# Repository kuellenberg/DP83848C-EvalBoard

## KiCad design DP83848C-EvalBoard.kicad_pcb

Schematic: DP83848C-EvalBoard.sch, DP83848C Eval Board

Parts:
H1, H2, H3, H4: MountingHole_Pad; MountingHole_3.2mm_M3_Pad_Via

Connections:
Earth: H1.1, H2.1, H3.1, H4.1; also elsewhere on the board

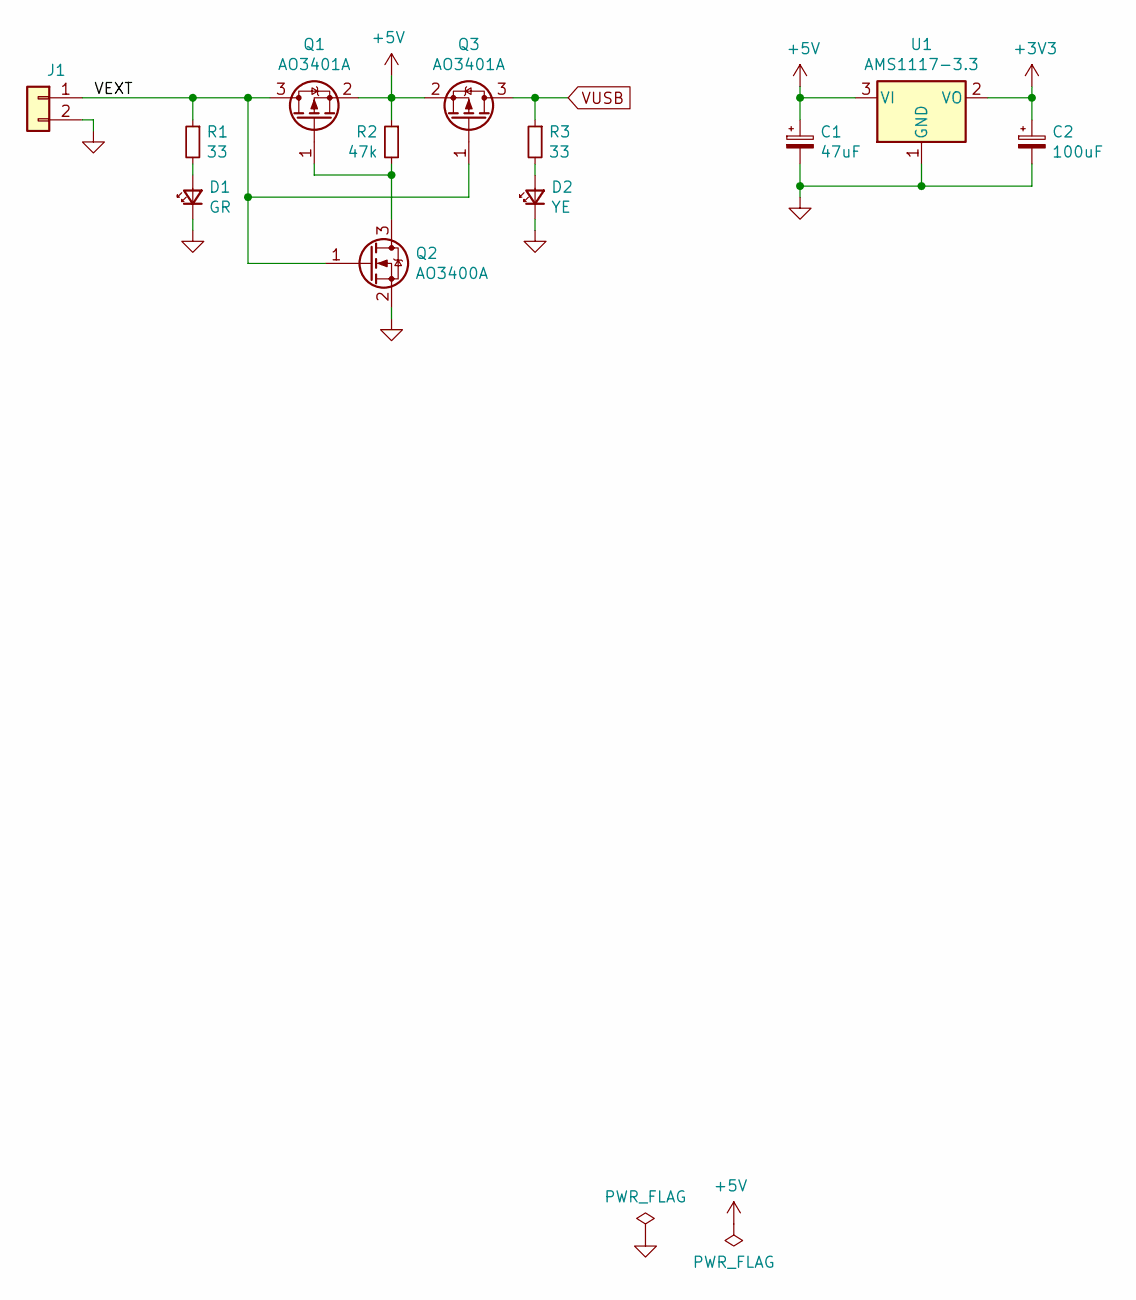
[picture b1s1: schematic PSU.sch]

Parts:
C1: 47uF; C_Elec_6.3x5.8; LCSC C178565
C2: 100uF; CP_EIA-3528-15_AVX-H; LCSC C16133
D1: GR; LED_0603_1608Metric; LCSC C72043
D2: YE; LED_0603_1608Metric; LCSC C72038
J1: Conn_01x02; Molex_022112022; Mouser 538-22-11-2022
Q1, Q3: AO3401A; SOT-23; LCSC C15127
Q2: AO3400A; SOT-23; LCSC C20917
R1, R3: 33; R_0402_1005Metric; LCSC C25105
R2: 47k; R_0402_1005Metric; LCSC C25792
U1: AMS1117-3.3; SOT-223-3_TabPin2; LCSC C6186

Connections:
+3V3: C2.1, U1.2 (VO); also elsewhere on the board
+5V: C1.1, Q1.2 (S), Q3.2 (S), R2.1, U1.3 (VI)
/PSU/VEXT: J1.1, Q1.3 (D), Q2.1 (G), Q3.1 (G), R1.1
GND: C1.2, C2.2, D1.1 (K), D2.1 (K), J1.2, Q2.2 (S), U1.1 (GND); also elsewhere on the board
unnamed: D1.2 (A), R1.2
unnamed: D2.2 (A), R3.2
unnamed: Q1.1 (G), Q2.3 (D), R2.2
VUSB: Q3.3 (D), R3.1; also elsewhere on the board

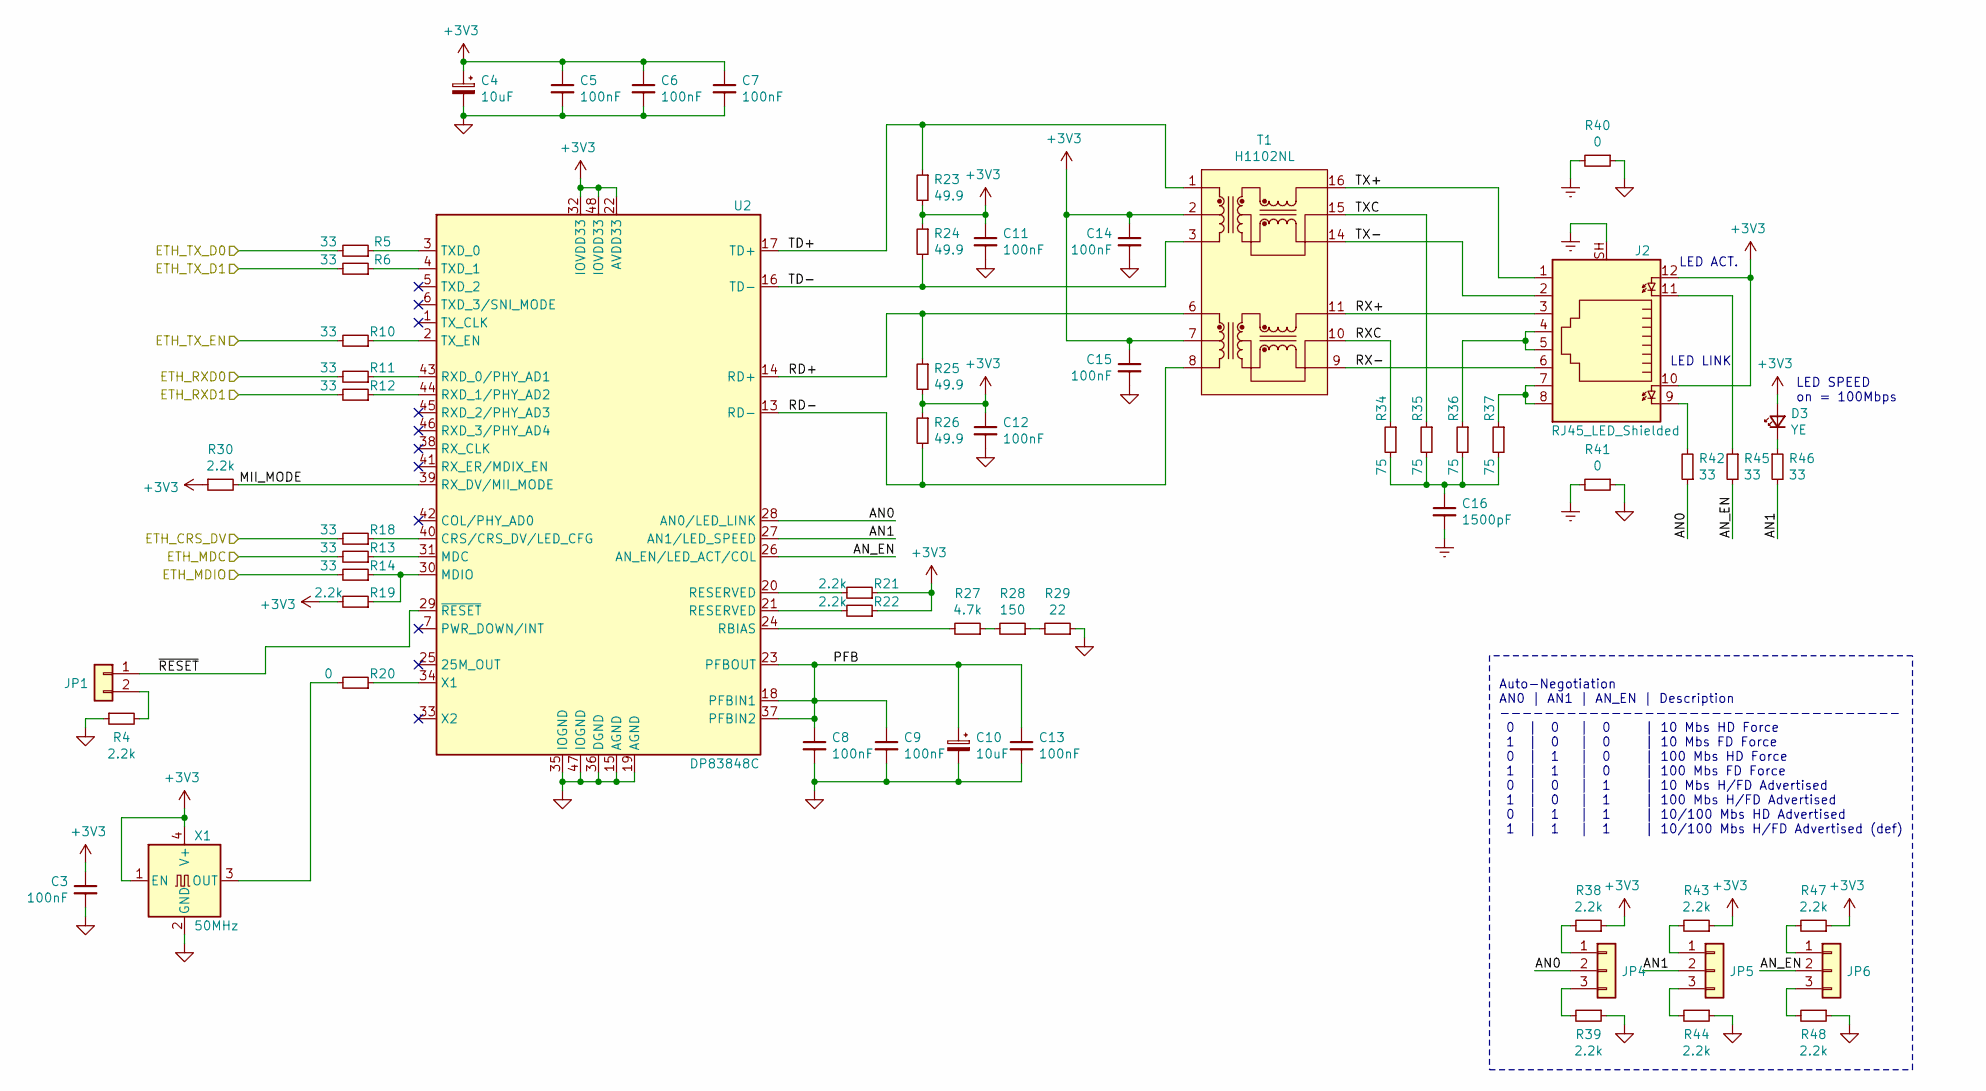
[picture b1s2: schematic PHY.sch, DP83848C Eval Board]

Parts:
C3, C5, C6, C7, C8, C9, C11, C12, C13, C14, C15: 100nF; C_0402_1005Metric; LCSC C1525
C4, C10: 10uF; CP_EIA-3216-18_Kemet-A; LCSC C7171
C16: 1500pF; C_0402_1005Metric; LCSC C23967
D3: YE; LED_0603_1608Metric; LCSC C72038
J2: RJ45_LED_Shielded; RJ45_Amphenol_RJHSE538X
JP1: Conn_01x02; PinHeader_1x02_P2.54mm_Vertical
JP4, JP5, JP6: Conn_01x03; PinHeader_1x03_P2.54mm_Vertical
R4, R19, R21, R22, R30, R38, R39, R43, R44, R47, R48: 2.2k; R_0402_1005Metric; LCSC C25879
R5, R6, R10, R11, R12, R13, R14, R18, R42, R45, R46: 33; R_0402_1005Metric; LCSC C25105
R20: 0; R_0402_1005Metric; LCSC C17168
R23, R24, R25, R26: 49.9; R_0402_1005Metric; LCSC C25120
R27: 4.7k; R_0402_1005Metric; LCSC C25900
R28: 150; R_0402_1005Metric; LCSC C25082
R29: 22; R_0402_1005Metric; LCSC C25092
R34, R35, R36, R37: 75; R_0402_1005Metric; LCSC C25133
R40, R41: 0; R_1206_3216Metric; LCSC C17888
T1: H1102NL; Transformer_Pulse_H1100NL; LCSC C18584
U2: DP83848C; LQFP-48_7x7mm_P0.5mm; LCSC C16688
X1: 50MHz; Oscillator_SMD_EuroQuartz_XO32-4Pin_3.2x2.5mm; LCSC C717684

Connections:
+3V3: C3.1, C4.1, C5.1, C6.1, C7.1, C11.1, C12.1, C14.1, C15.1, D3.2 (A), J2.10, J2.12, R19.2, R21.1, R22.1, R23.2, R24.1, R25.2, R26.1, R30.1, R38.1, R43.1, R47.1, T1.2, T1.7, U2.22 (AVDD33), U2.32 (IOVDD33), U2.48 (IOVDD33), X1.1 (EN), X1.4 (V+); also elsewhere on the board
/ETH_CRS_DV: R18.2; also elsewhere on the board
/ETH_MDC: R13.2; also elsewhere on the board
/ETH_MDIO: R14.2; also elsewhere on the board
/ETH_RXD0: R11.2; also elsewhere on the board
/ETH_RXD1: R12.2; also elsewhere on the board
/ETH_TX_D0: R5.2; also elsewhere on the board
/ETH_TX_D1: R6.2; also elsewhere on the board
/ETH_TX_EN: R10.2; also elsewhere on the board
/PHY/AN0: JP4.2, R42.1, U2.28 (AN0/LED_LINK)
/PHY/AN1: JP5.2, R46.2, U2.27 (AN1/LED_SPEED)
/PHY/AN_EN: JP6.2, R45.2, U2.26 (AN_EN/LED_ACT/COL)
/PHY/MII_MODE: R30.2, U2.39 (RX_DV/MII_MODE)
/PHY/PFB: C8.1, C9.1, C10.1, C13.1, U2.18 (PFBIN1), U2.23 (PFBOUT), U2.37 (PFBIN2)
/PHY/RD+: R25.1, T1.6, U2.14 (RD+)
/PHY/RD-: R26.2, T1.8, U2.13 (RD-)
/PHY/RX+: J2.3, T1.11
/PHY/RX-: J2.6, T1.9
/PHY/RXC: R34.1, T1.10
/PHY/TD+: R23.1, T1.1, U2.17 (TD+)
/PHY/TD-: R24.2, T1.3, U2.16 (TD-)
/PHY/TX+: J2.1, T1.16
/PHY/TX-: J2.2, T1.14
/PHY/TXC: R35.1, T1.15
/PHY/~RESET: JP1.1, U2.29 (~RESET~)
Earth: C16.2, J2.SH, R40.2, R41.2; also elsewhere on the board
GND: C3.2, C4.2, C5.2, C6.2, C7.2, C8.2, C9.2, C10.2, C11.2, C12.2, C13.2, C14.2, C15.2, R4.1, R29.1, R39.1, R40.1, R41.1, R44.1, R48.1, U2.15 (AGND), U2.19 (AGND), U2.35 (IOGND), U2.36 (DGND), U2.47 (IOGND), X1.2 (GND); also elsewhere on the board
unnamed: C16.1, R34.2, R35.2, R36.2, R37.2
unnamed: D3.1 (K), R46.1
unnamed: J2.4, J2.5, R36.1
unnamed: J2.7, J2.8, R37.1
unnamed: J2.9, R42.2
unnamed: J2.11, R45.1
unnamed: JP1.2, R4.2
unnamed: JP4.1, R38.2
unnamed: JP4.3, R39.2
unnamed: JP5.1, R43.2
unnamed: JP5.3, R44.2
unnamed: JP6.1, R47.2
unnamed: JP6.3, R48.2
unnamed: R5.1, U2.3 (TXD_0)
unnamed: R6.1, U2.4 (TXD_1)
unnamed: R10.1, U2.2 (TX_EN)
unnamed: R11.1, U2.43 (RXD_0/PHY_AD1)
unnamed: R12.1, U2.44 (RXD_1/PHY_AD2)
unnamed: R13.1, U2.31 (MDC)
unnamed: R14.1, R19.1, U2.30 (MDIO)
unnamed: R18.1, U2.40 (CRS/CRS_DV/LED_CFG)
unnamed: R20.1, U2.34 (X1)
unnamed: R20.2, X1.3 (OUT)
unnamed: R21.2, U2.20 (RESERVED)
unnamed: R22.2, U2.21 (RESERVED)
unnamed: R27.1, R28.2
unnamed: R27.2, U2.24 (RBIAS)
unnamed: R28.1, R29.2

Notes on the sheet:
Auto-Negotiation AN0 | AN1 | AN_EN | Description ------------------------------------ 0 | 0 | 0 | 10 Mbs HD Force 1 | 0 | 0 | 10 Mbs FD Force 0 | 1 | 0 | 100 Mbs HD Force 1 | 1 | 0 | 100 Mbs FD Force 0 | 0 | 1 | 10 Mbs H/FD Advertised 1 | 0 | 1 | 100 Mbs H/FD Advertised 0 | 1 | 1 | 10/100 Mbs HD Ad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
LED ACT.
LED LINK
LED SPEED on = 100Mbps

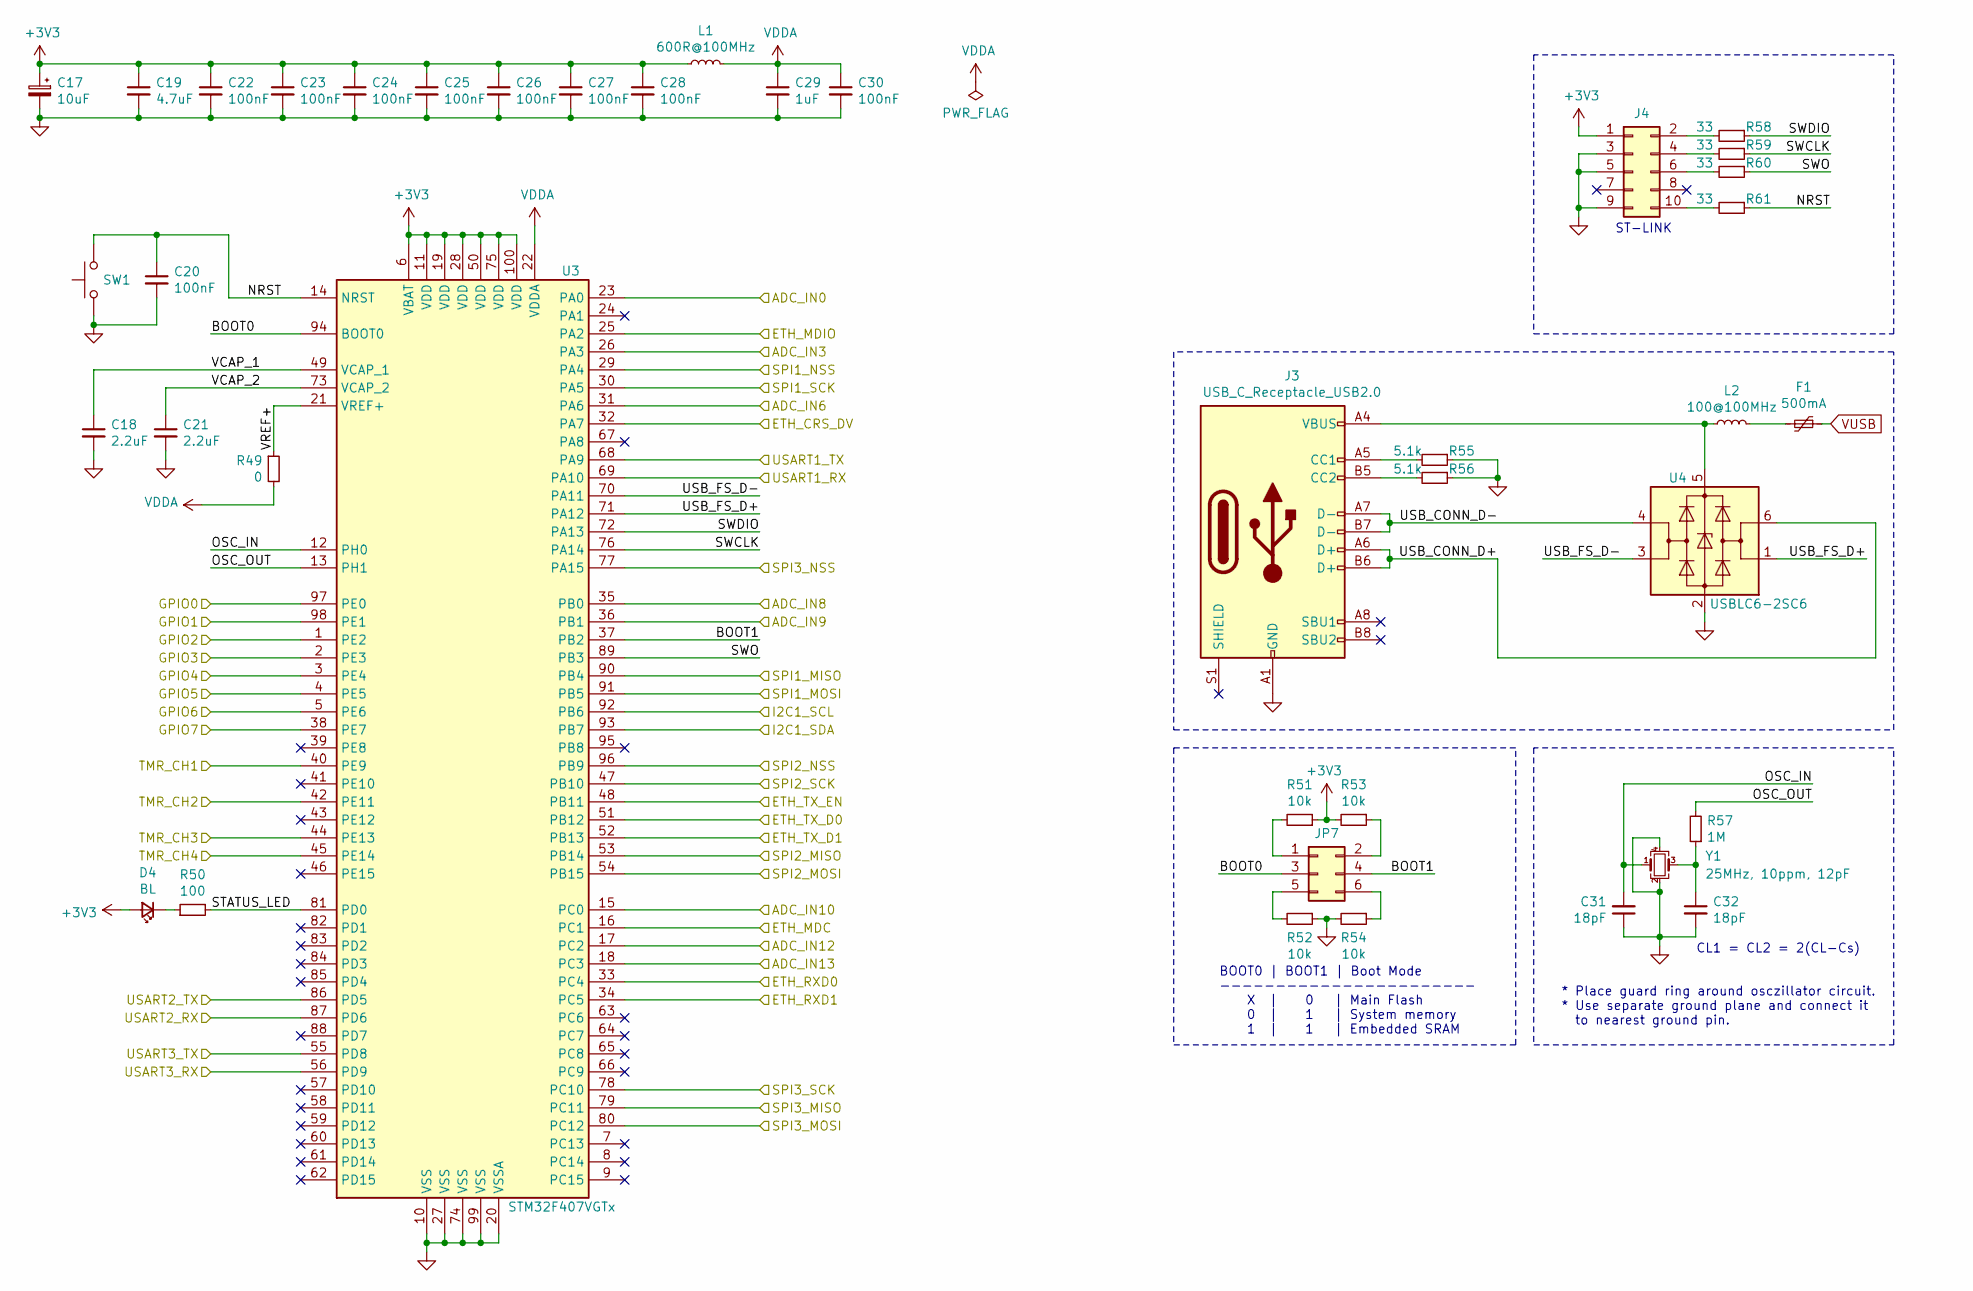
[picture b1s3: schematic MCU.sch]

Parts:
C17: 10uF; CP_EIA-3216-18_Kemet-A; LCSC C7171
C18, C21: 2.2uF; C_0603_1608Metric; LCSC C23630
C19: 4.7uF; C_0402_1005Metric; LCSC C23733
C20, C22, C23, C24, C25, C26, C27, C28, C30: 100nF; C_0402_1005Metric; LCSC C1525
C29: 1uF; C_0402_1005Metric; LCSC C52923
C31, C32: 18pF; C_0402_1005Metric; LCSC C1549
D4: BL; LED_0603_1608Metric; LCSC C72041
F1: 500mA; Fuse_1812_4532Metric_Castellated; Mouser 576-1812L050/60MR
J3: USB_C_Receptacle_USB2.0; DX07S016JA3R1500; Mouser 656-DX07S016JA3R1500
J4: Conn_02x05_Odd_Even; PinHeader_2x05_P2.54mm_Vertical
JP7: Conn_02x03_Odd_Even; PinHeader_2x03_P2.54mm_Vertical
L1: 600R@100MHz; L_0805_2012Metric; LCSC C1002
L2: 100@100MHz; L_0805_2012Metric; LCSC C1015
R49: 0; R_0402_1005Metric; LCSC C17168
R50: 100; R_0402_1005Metric; LCSC C25076
R51, R52, R53, R54: 10k; R_0402_1005Metric; LCSC C25744
R55, R56: 5.1k; R_0402_1005Metric; LCSC C25905
R57: 1M; R_0402_1005Metric; LCSC C26083
R58, R59, R60, R61: 33; R_0402_1005Metric; LCSC C25105
SW1: SW_Push; SW_PUSH_6mm; Mouser 611-PTS645SK432
U3: STM32F407VGTx; LQFP-100_14x14mm_P0.5mm; LCSC C28730
U4: USBLC6-2SC6; SOT-23-6; LCSC C558442
Y1: 25MHz, 10ppm, 12pF; Crystal_SMD_3225-4Pin_3.2x2.5mm; LCSC C9006

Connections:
+3V3: C17.1, C19.1, C22.1, C23.1, C24.1, C25.1, C26.1, C27.1, C28.1, D4.2 (A), J4.1, L1.1, R51.1, R53.2, U3.6 (VBAT), U3.11 (VDD), U3.19 (VDD), U3.28 (VDD), U3.50 (VDD), U3.75 (VDD), U3.100 (VDD); also elsewhere on the board
/ETH_CRS_DV: U3.32 (PA7); also elsewhere on the board
/ETH_MDC: U3.16 (PC1); also elsewhere on the board
/ETH_MDIO: U3.25 (PA2); also elsewhere on the board
/ETH_RXD0: U3.33 (PC4); also elsewhere on the board
/ETH_RXD1: U3.34 (PC5); also elsewhere on the board
/ETH_TX_D0: U3.51 (PB12); also elsewhere on the board
/ETH_TX_D1: U3.52 (PB13); also elsewhere on the board
/ETH_TX_EN: U3.48 (PB11); also elsewhere on the board
/IO/ADC0: U3.23 (PA0); also elsewhere on the board
/IO/ADC1: U3.26 (PA3); also elsewhere on the board
/IO/ADC2: U3.31 (PA6); also elsewhere on the board
/IO/ADC3: U3.35 (PB0); also elsewhere on the board
/IO/ADC4: U3.36 (PB1); also elsewhere on the board
/IO/ADC5: U3.15 (PC0); also elsewhere on the board
/IO/ADC6: U3.17 (PC2); also elsewhere on the board
/IO/ADC7: U3.18 (PC3); also elsewhere on the board
/IO/GPIO0: U3.97 (PE0); also elsewhere on the board
/IO/GPIO1: U3.98 (PE1); also elsewhere on the board
/IO/GPIO2: U3.1 (PE2); also elsewhere on the board
/IO/GPIO3: U3.2 (PE3); also elsewhere on the board
/IO/GPIO4: U3.3 (PE4); also elsewhere on the board
/IO/GPIO5: U3.4 (PE5); also elsewhere on the board
/IO/GPIO6: U3.5 (PE6); also elsewhere on the board
/IO/GPIO7: U3.38 (PE7); also elsewhere on the board
/IO/I2C1_SCL: U3.92 (PB6); also elsewhere on the board
/IO/I2C1_SDA: U3.93 (PB7); also elsewhere on the board
/IO/SPI1_MISO: U3.90 (PB4); also elsewhere on the board
/IO/SPI1_MOSI: U3.91 (PB5); also elsewhere on the board
/IO/SPI1_NSS: U3.29 (PA4); also elsewhere on the board
/IO/SPI1_SCK: U3.30 (PA5); also elsewhere on the board
/IO/SPI2_MISO: U3.53 (PB14); also elsewhere on the board
/IO/SPI2_MOSI: U3.54 (PB15); also elsewhere on the board
/IO/SPI2_NSS: U3.96 (PB9); also elsewhere on the board
/IO/SPI2_SCK: U3.47 (PB10); also elsewhere on the board
/IO/SPI3_MISO: U3.79 (PC11); also elsewhere on the board
/IO/SPI3_MOSI: U3.80 (PC12); also elsewhere on the board
/IO/SPI3_NSS: U3.77 (PA15); also elsewhere on the board
/IO/SPI3_SCK: U3.78 (PC10); also elsewhere on the board
/IO/TMR1: U3.40 (PE9); also elsewhere on the board
/IO/TMR2: U3.42 (PE11); also elsewhere on the board
/IO/TMR3: U3.44 (PE13); also elsewhere on the board
/IO/TMR4: U3.45 (PE14); also elsewhere on the board
/IO/USART1_RX: U3.69 (PA10); also elsewhere on the board
/IO/USART1_TX: U3.68 (PA9); also elsewhere on the board
/IO/USART2_RX: U3.87 (PD6); also elsewhere on the board
/IO/USART2_TX: U3.86 (PD5); also elsewhere on the board
/IO/USART3_RX: U3.56 (PD9); also elsewhere on the board
/IO/USART3_TX: U3.55 (PD8); also elsewhere on the board
/MCU/BOOT0: JP7.3, U3.94 (BOOT0)
/MCU/BOOT1: JP7.4, U3.37 (PB2)
/MCU/NRST: C20.1, R61.1, SW1.1, U3.14 (NRST)
/MCU/OSC_IN: C31.2, U3.12 (PH0), Y1.1
/MCU/OSC_OUT: R57.2, U3.13 (PH1)
/MCU/STATUS_LED: R50.2, U3.81 (PD0)
/MCU/SWCLK: R59.1, U3.76 (PA14)
/MCU/SWDIO: R58.1, U3.72 (PA13)
/MCU/SWO: R60.1, U3.89 (PB3)
/MCU/USB_CONN_D+: J3.A6 (D+), J3.B6 (D+), U4.6 (I/O1)
/MCU/USB_CONN_D-: J3.A7 (D-), J3.B7 (D-), U4.4 (I/O2)
/MCU/USB_FS_D+: U3.71 (PA12), U4.1 (I/O1)
/MCU/USB_FS_D-: U3.70 (PA11), U4.3 (I/O2)
/MCU/VCAP_1: C18.1, U3.49 (VCAP_1)
/MCU/VCAP_2: C21.1, U3.73 (VCAP_2)
/MCU/VREF+: R49.1, U3.21 (VREF+)
Earth: J3.S1 (SHIELD); also elsewhere on the board
GND: C17.2, C18.2, C19.2, C20.2, C21.2, C22.2, C23.2, C24.2, C25.2, C26.2, C27.2, C28.2, C29.2, C30.2, C31.1, C32.2, J3.A1 (GND), J3.A12 (GND), J3.B1 (GND), J3.B12 (GND), J4.3, J4.5, J4.9, R52.1, R54.2, R55.1, R56.1, SW1.2, U3.10 (VSS), U3.20 (VSSA), U3.27 (VSS), U3.74 (VSS), U3.99 (VSS), U4.2 (GND), Y1.2, Y1.4; also elsewhere on the board
unnamed: C32.1, R57.1, Y1.3
unnamed: D4.1 (K), R50.1
unnamed: F1.2, L2.2
unnamed: J3.A4 (VBUS), J3.A9 (VBUS), J3.B4 (VBUS), J3.B9 (VBUS), L2.1, U4.5 (VBUS)
unnamed: J3.A5 (CC1), R55.2
unnamed: J3.B5 (CC2), R56.2
unnamed: J4.2, R58.2
unnamed: J4.4, R59.2
unnamed: J4.6, R60.2
unnamed: J4.10, R61.2
unnamed: JP7.1, R51.2
unnamed: JP7.2, R53.1
unnamed: JP7.5, R52.2
unnamed: JP7.6, R54.1
VDDA: C29.1, C30.1, L1.2, R49.2, U3.22 (VDDA)
VUSB: F1.1; also elsewhere on the board

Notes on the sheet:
BOOT0 | BOOT1 | Boot Mode ----------------------- X | 0 | Main Flash 0 | 1 | System memory 1 | 1 | Embedded SRAM
ST-LINK
* Place guard ring around osczillator circuit. * Use separate ground plane and connect it to nearest ground pin.
CL1 = CL2 = 2(CL-Cs)

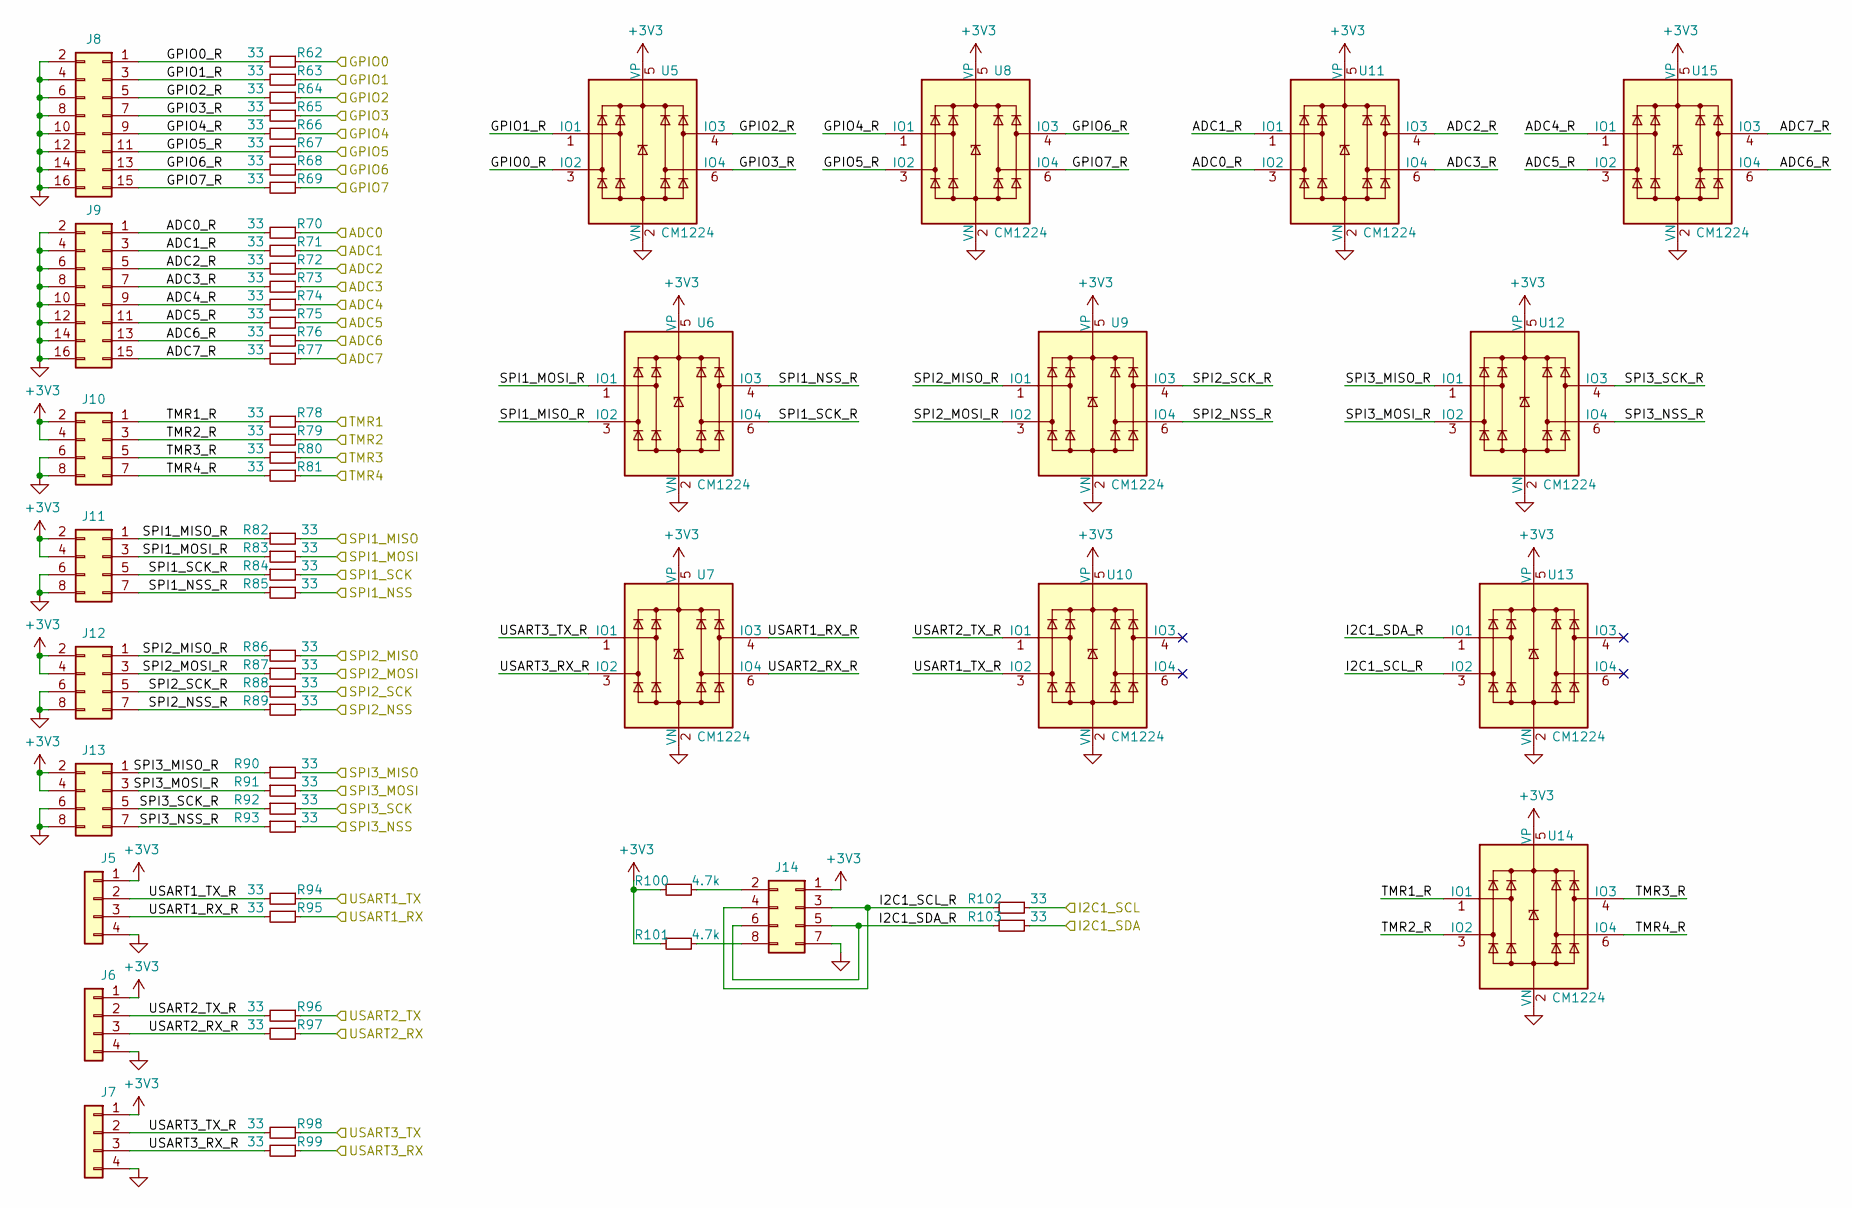
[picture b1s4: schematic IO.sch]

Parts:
J5, J6, J7: Conn_01x04; PinHeader_1x04_P2.54mm_Vertical
J8, J9: Conn_02x08_Odd_Even; PinHeader_2x08_P2.54mm_Vertical
J10, J11, J12, J13, J14: Conn_02x04_Odd_Even; PinHeader_2x04_P2.54mm_Vertical
R62, R63, R64, R65, R66, R67, R68, R69, R70, R71, R72, R73, R74, R75, R76, R77, R78, R79, R80, R81, R82, R83, R84, R85, R86, R87, R88, R89, R90, R91, R92, R93, R94, R95, R96, R97, R98, R99, R102, R103: 33; R_0402_1005Metric; LCSC C25105
R100, R101: 4.7k; R_0402_1005Metric; LCSC C25900
U5, U6, U7, U8, U9, U10, U11, U12, U13, U14, U15: CM1224; SOT-23-6; LCSC C233379

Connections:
+3V3: J5.1, J6.1, J7.1, J10.2, J10.4, J11.2, J11.4, J12.2, J12.4, J13.2, J13.4, J14.1, R100.1, R101.1, U5.5 (VP), U6.5 (VP), U7.5 (VP), U8.5 (VP), U9.5 (VP), U10.5 (VP), U11.5 (VP), U12.5 (VP), U13.5 (VP), U14.5 (VP), U15.5 (VP); also elsewhere on the board
/IO/ADC0: R70.1; also elsewhere on the board
/IO/ADC0_R: J9.1, R70.2, U11.3 (IO2)
/IO/ADC1: R71.1; also elsewhere on the board
/IO/ADC1_R: J9.3, R71.2, U11.1 (IO1)
/IO/ADC2: R72.1; also elsewhere on the board
/IO/ADC2_R: J9.5, R72.2, U11.4 (IO3)
/IO/ADC3: R73.1; also elsewhere on the board
/IO/ADC3_R: J9.7, R73.2, U11.6 (IO4)
/IO/ADC4: R74.1; also elsewhere on the board
/IO/ADC4_R: J9.9, R74.2, U15.1 (IO1)
/IO/ADC5: R75.1; also elsewhere on the board
/IO/ADC5_R: J9.11, R75.2, U15.3 (IO2)
/IO/ADC6: R76.1; also elsewhere on the board
/IO/ADC6_R: J9.13, R76.2, U15.6 (IO4)
/IO/ADC7: R77.1; also elsewhere on the board
/IO/ADC7_R: J9.15, R77.2, U15.4 (IO3)
/IO/GPIO0: R62.1; also elsewhere on the board
/IO/GPIO0_R: J8.1, R62.2, U5.3 (IO2)
/IO/GPIO1: R63.1; also elsewhere on the board
/IO/GPIO1_R: J8.3, R63.2, U5.1 (IO1)
/IO/GPIO2: R64.1; also elsewhere on the board
/IO/GPIO2_R: J8.5, R64.2, U5.4 (IO3)
/IO/GPIO3: R65.1; also elsewhere on the board
/IO/GPIO3_R: J8.7, R65.2, U5.6 (IO4)
/IO/GPIO4: R66.1; also elsewhere on the board
/IO/GPIO4_R: J8.9, R66.2, U8.1 (IO1)
/IO/GPIO5: R67.1; also elsewhere on the board
/IO/GPIO5_R: J8.11, R67.2, U8.3 (IO2)
/IO/GPIO6: R68.1; also elsewhere on the board
/IO/GPIO6_R: J8.13, R68.2, U8.4 (IO3)
/IO/GPIO7: R69.1; also elsewhere on the board
/IO/GPIO7_R: J8.15, R69.2, U8.6 (IO4)
/IO/I2C1_SCL: R102.2; also elsewhere on the board
/IO/I2C1_SCL_R: J14.3, J14.4, R102.1, U13.3 (IO2)
/IO/I2C1_SDA: R103.2; also elsewhere on the board
/IO/I2C1_SDA_R: J14.5, J14.6, R103.1, U13.1 (IO1)
/IO/SPI1_MISO: R82.2; also elsewhere on the board
/IO/SPI1_MISO_R: J11.1, R82.1, U6.3 (IO2)
/IO/SPI1_MOSI: R83.2; also elsewhere on the board
/IO/SPI1_MOSI_R: J11.3, R83.1, U6.1 (IO1)
/IO/SPI1_NSS: R85.2; also elsewhere on the board
/IO/SPI1_NSS_R: J11.7, R85.1, U6.4 (IO3)
/IO/SPI1_SCK: R84.2; also elsewhere on the board
/IO/SPI1_SCK_R: J11.5, R84.1, U6.6 (IO4)
/IO/SPI2_MISO: R86.2; also elsewhere on the board
/IO/SPI2_MISO_R: J12.1, R86.1, U9.1 (IO1)
/IO/SPI2_MOSI: R87.2; also elsewhere on the board
/IO/SPI2_MOSI_R: J12.3, R87.1, U9.3 (IO2)
/IO/SPI2_NSS: R89.2; also elsewhere on the board
/IO/SPI2_NSS_R: J12.7, R89.1, U9.6 (IO4)
/IO/SPI2_SCK: R88.2; also elsewhere on the board
/IO/SPI2_SCK_R: J12.5, R88.1, U9.4 (IO3)
/IO/SPI3_MISO: R90.2; also elsewhere on the board
/IO/SPI3_MISO_R: J13.1, R90.1, U12.1 (IO1)
/IO/SPI3_MOSI: R91.2; also elsewhere on the board
/IO/SPI3_MOSI_R: J13.3, R91.1, U12.3 (IO2)
/IO/SPI3_NSS: R93.2; also elsewhere on the board
/IO/SPI3_NSS_R: J13.7, R93.1, U12.6 (IO4)
/IO/SPI3_SCK: R92.2; also elsewhere on the board
/IO/SPI3_SCK_R: J13.5, R92.1, U12.4 (IO3)
/IO/TMR1: R78.1; also elsewhere on the board
/IO/TMR1_R: J10.1, R78.2, U14.1 (IO1)
/IO/TMR2: R79.1; also elsewhere on the board
/IO/TMR2_R: J10.3, R79.2, U14.3 (IO2)
/IO/TMR3: R80.1; also elsewhere on the board
/IO/TMR3_R: J10.5, R80.2, U14.4 (IO3)
/IO/TMR4: R81.1; also elsewhere on the board
/IO/TMR4_R: J10.7, R81.2, U14.6 (IO4)
/IO/USART1_RX: R95.1; also elsewhere on the board
/IO/USART1_RX_R: J5.3, R95.2, U7.4 (IO3)
/IO/USART1_TX: R94.1; also elsewhere on the board
/IO/USART1_TX_R: J5.2, R94.2, U10.3 (IO2)
/IO/USART2_RX: R97.1; also elsewhere on the board
/IO/USART2_RX_R: J6.3, R97.2, U7.6 (IO4)
/IO/USART2_TX: R96.1; also elsewhere on the board
/IO/USART2_TX_R: J6.2, R96.2, U10.1 (IO1)
/IO/USART3_RX: R99.1; also elsewhere on the board
/IO/USART3_RX_R: J7.3, R99.2, U7.3 (IO2)
/IO/USART3_TX: R98.1; also elsewhere on the board
/IO/USART3_TX_R: J7.2, R98.2, U7.1 (IO1)
GND: J5.4, J6.4, J7.4, J8.2, J8.4, J8.6, J8.8, J8.10, J8.12, J8.14, J8.16, J9.2, J9.4, J9.6, J9.8, J9.10, J9.12, J9.14, J9.16, J10.6, J10.8, J11.6, J11.8, J12.6, J12.8, J13.6, J13.8, J14.7, U5.2 (VN), U6.2 (VN), U7.2 (VN), U8.2 (VN), U9.2 (VN), U10.2 (VN), U11.2 (VN), U12.2 (VN), U13.2 (VN), U14.2 (VN), U15.2 (VN); also elsewhere on the board
unnamed: J14.2, R100.2
unnamed: J14.8, R101.2

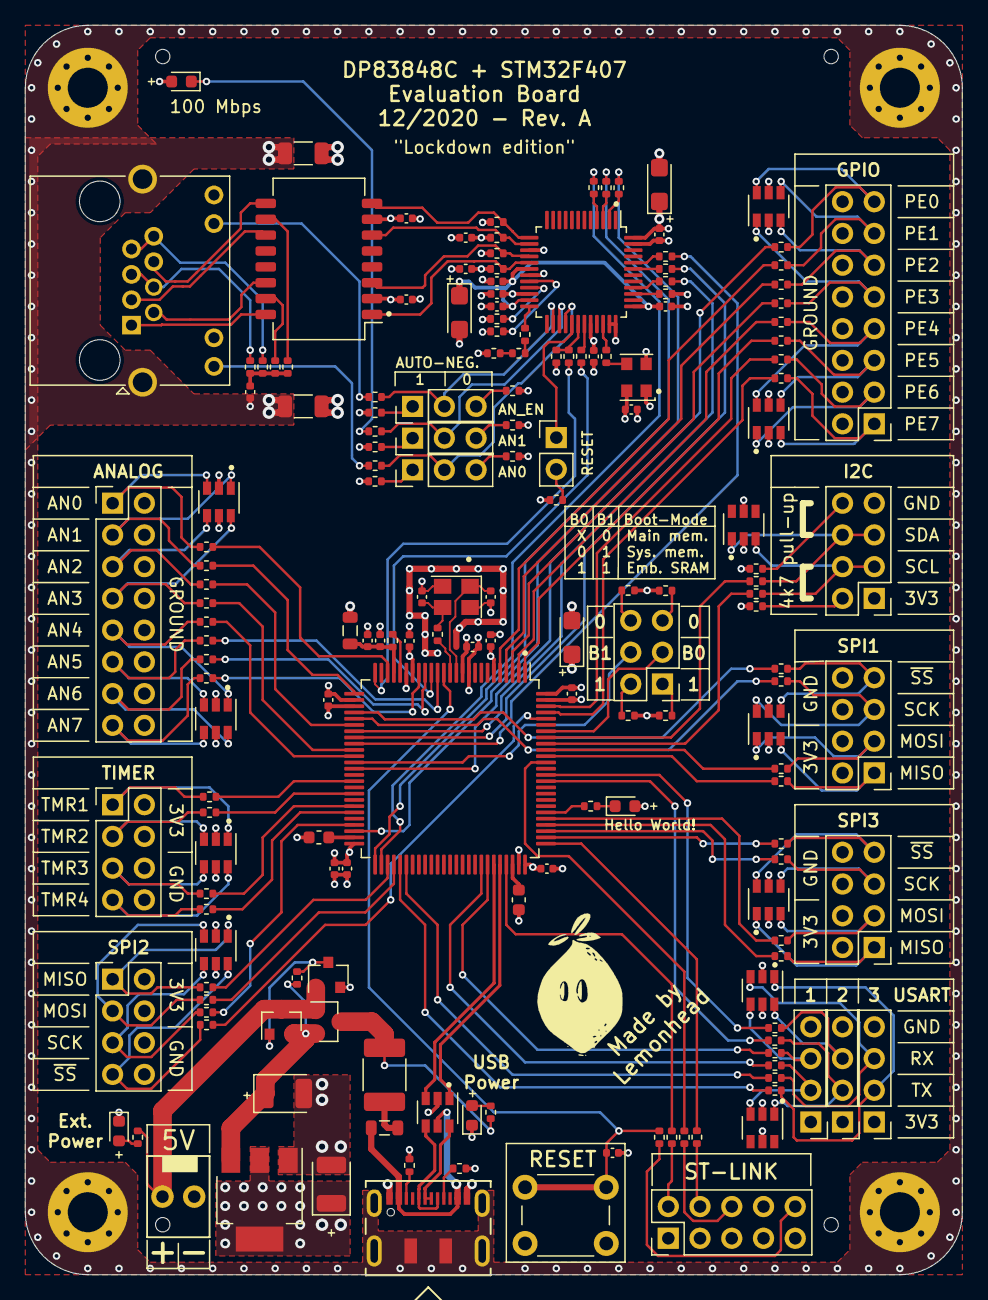
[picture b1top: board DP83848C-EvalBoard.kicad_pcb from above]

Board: 4 copper layers, 75.0 x 100.0 mm, 178 parts (0 on the bottom side), 174 nets.
